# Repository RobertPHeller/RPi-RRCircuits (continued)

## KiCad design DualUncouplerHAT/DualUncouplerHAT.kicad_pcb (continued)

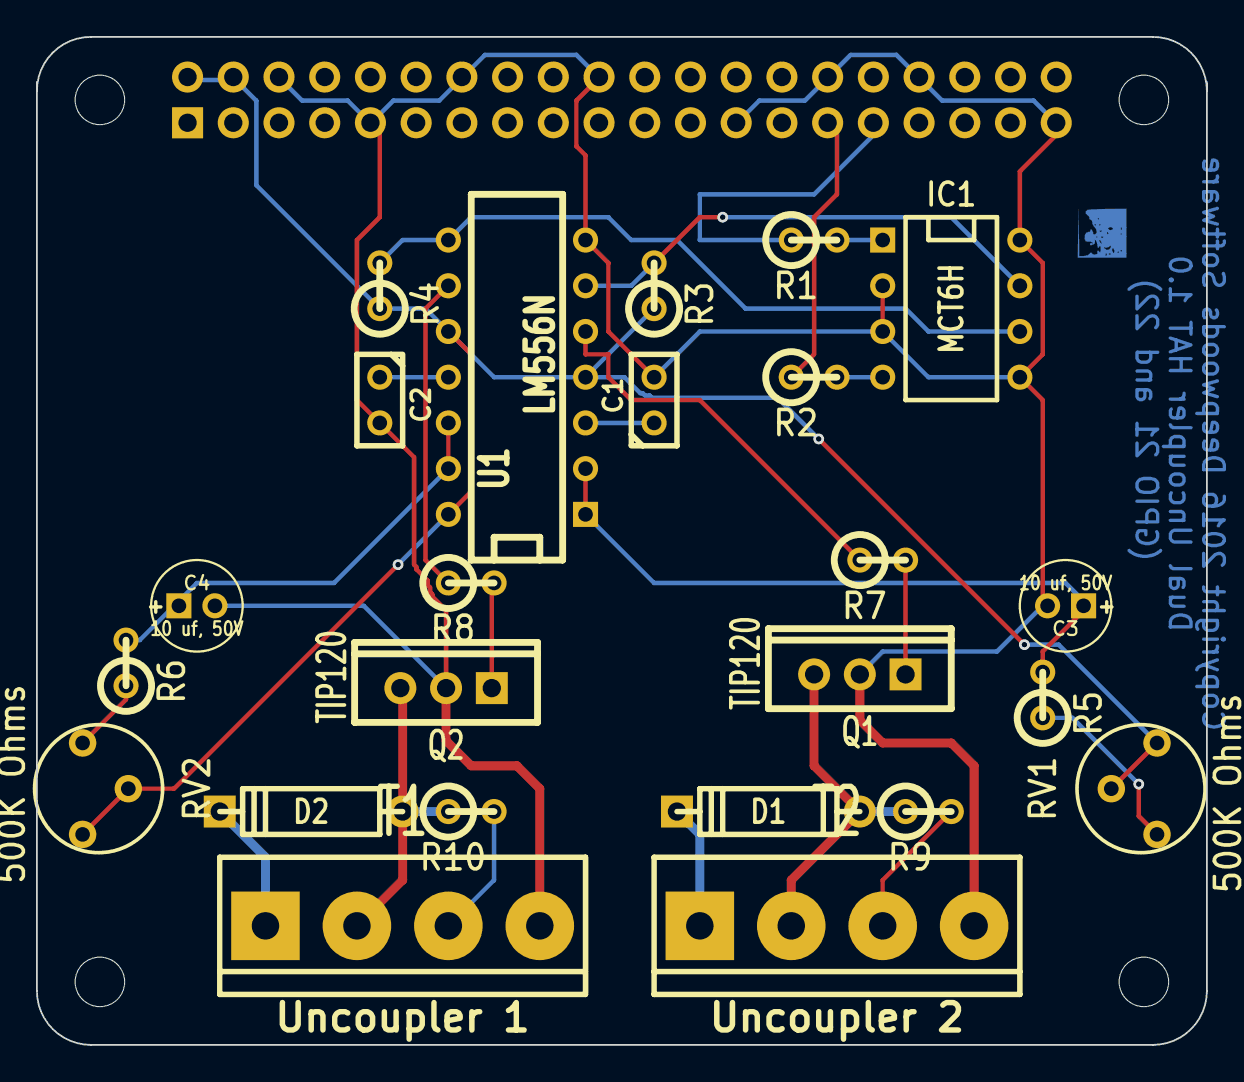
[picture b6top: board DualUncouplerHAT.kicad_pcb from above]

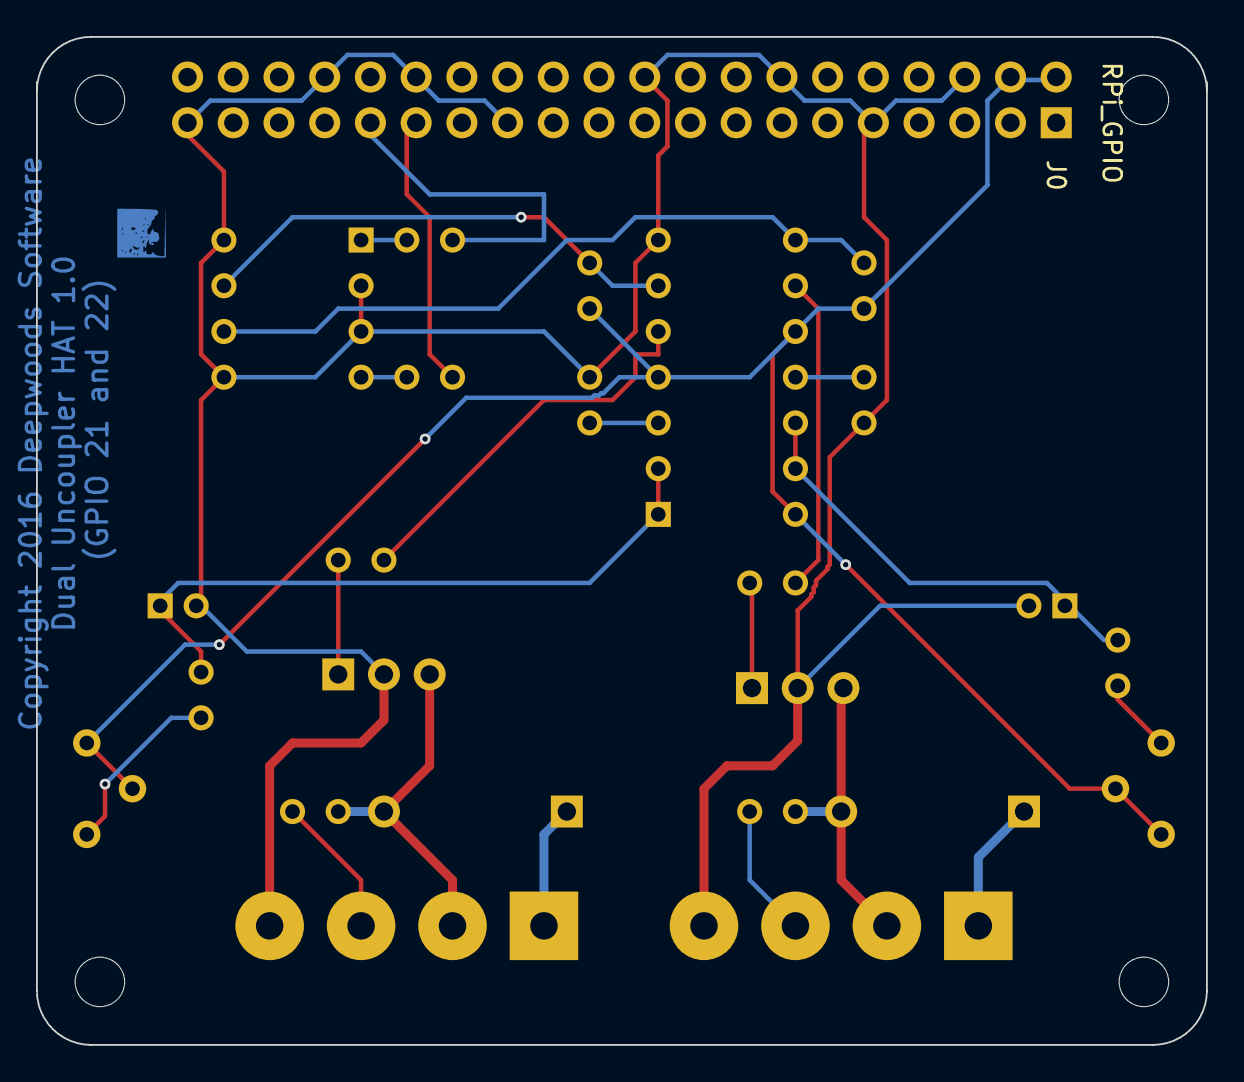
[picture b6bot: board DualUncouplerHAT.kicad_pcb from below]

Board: 2 copper layers, 65.0 x 56.0 mm, 29 parts (5 on the bottom side), 24 nets.

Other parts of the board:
H1, H2, H3, H4: RPi_Hat_Mounting_Hole
